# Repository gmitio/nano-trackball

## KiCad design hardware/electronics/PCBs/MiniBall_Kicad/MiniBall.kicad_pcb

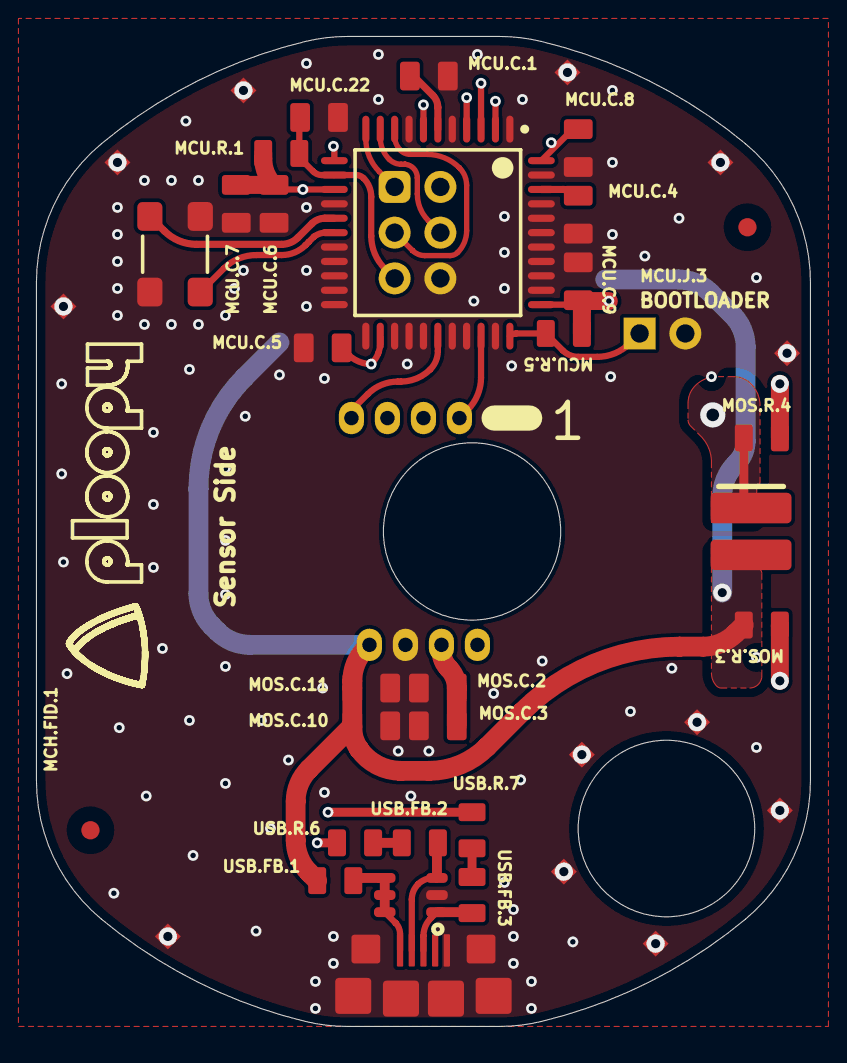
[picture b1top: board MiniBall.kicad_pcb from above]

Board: 4 copper layers, 43.0 x 55.0 mm, 44 parts (0 on the bottom side), 24 nets.

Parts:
MCH.FID.1, MCH.FID.2: IPC-7351 Fiducial 1mm; FIDUCIAL_1.5
MCH.LOGO.1: Ploopy logo, silkscreen; PloopyLogo
MCH.SP.1, MCH.SP.2, MCH.SP.3, MCH.SP.4, MCH.SP.5, MCH.SP.6, MCH.SP.7, MCH.SP.8, MCH.SP.9, MCH.SP.10, MCH.SP.11, MCH.SP.12: Spark Gap; SparkGap
MCU.C.1, MCU.C.4, MCU.C.5, MCU.C.6, MCU.C.7, MCU.C.8, MCU.C.9, MCU.C.22: 0805; 0805 - TALL
MCU.J.1: Atmel_ICSP; 6x2
MCU.J.3: HEADER2; 2x1
MCU.R.1, MCU.R.5: 0805
MCU.U.1: ATMEGA32U4RC-AU; ATmega32U4 - TQFP80P1200X1200X120-44N
MCU.Y.1: ECS-160-12-30B-AGM; LFXTAL055663BULK
MOS.C.2, MOS.C.3, MOS.C.10, MOS.C.11: 0805; 0805 - TALL
MOS.D.1: SIDELED-A67F
MOS.R.3, MOS.R.4: 0805
MOS.U.2: ADNS-5050
USB.FB.1, USB.FB.2, USB.FB.3: ACML-0805-601-T; 0805
USB.J.2: 10118192-0001LF
USB.R.6, USB.R.7: 0805
USB.Z.1: IP4220CZ6,125; PESD3V3S4UD - SOT95P275X110-6N

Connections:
GND: MCH.SP.1.1, MCH.SP.2.1, MCH.SP.3.1, MCH.SP.4.1, MCH.SP.5.1, MCH.SP.6.1, MCH.SP.7.1, MCH.SP.8.1, MCH.SP.9.1, MCH.SP.10.1, MCH.SP.11.1, MCH.SP.12.1, MCU.C.1.1, MCU.C.4.1, MCU.C.5.1, MCU.C.6.1, MCU.C.7.1, MCU.C.8.1, MCU.C.9.1, MCU.C.22.1, MCU.J.1.6, MCU.J.3.2, MCU.U.1.1, MCU.U.1.5, MCU.U.1.8, MCU.U.1.15, MCU.U.1.18, MCU.U.1.19, MCU.U.1.20, MCU.U.1.21, MCU.U.1.22, MCU.U.1.23, MCU.U.1.25, MCU.U.1.26, MCU.U.1.27, MCU.U.1.29, MCU.U.1.30, MCU.U.1.32, MCU.U.1.35, MCU.U.1.36, MCU.U.1.37, MCU.U.1.38, MCU.U.1.39, MCU.U.1.40, MCU.U.1.41, MCU.U.1.43, MCU.Y.1.2, MCU.Y.1.4, MOS.C.2.1, MOS.C.3.1, MOS.C.10.1, MOS.C.11.1, MOS.U.2.6, USB.J.2.5, USB.J.2.6, USB.Z.1.2
MISO: MCU.J.1.1, MCU.U.1.11
MOSI: MCU.J.1.4, MCU.U.1.10
NetMCU.C.1_2: MCU.C.1.2, MCU.U.1.6
NetMCU.C.4_2: MCU.C.4.2, MCU.U.1.42
NetMCU.J.3_1: MCU.J.3.1, MCU.R.5.1, MCU.U.1.33
NetMCU.U.1_3: MCU.U.1.3, USB.R.6.2
NetMCU.U.1_4: MCU.U.1.4, USB.R.7.2
NetMCU.U.1_12: MCU.U.1.12, MOS.U.2.8
NetMCU.U.1_16: MCU.U.1.16, MCU.Y.1.1
NetMCU.U.1_17: MCU.U.1.17, MCU.Y.1.3
NetMCU.U.1_28: MCU.U.1.28, MOS.U.2.4
NetMCU.U.1_31: MCU.U.1.31, MOS.U.2.1
NetMOS.C.2_2: MOS.C.2.2, MOS.C.3.2, MOS.U.2.7
NetMOS.D.1_C: MOS.D.1.C, MOS.R.4.1, MOS.U.2.2
NetMOS.R.3_1: MOS.R.3.1, MOS.R.4.2
NetUSB.FB.1_1: USB.FB.1.1, USB.J.2.1, USB.Z.1.4, USB.Z.1.5, USB.Z.1.6
NetUSB.FB.2_1: USB.FB.2.1, USB.J.2.2, USB.Z.1.3
NetUSB.FB.2_2: USB.FB.2.2, USB.R.6.1
NetUSB.FB.3_1: USB.FB.3.1, USB.J.2.3, USB.Z.1.1
NetUSB.FB.3_2: USB.FB.3.2, USB.R.7.1
SCLK: MCU.J.1.3, MCU.U.1.9
V_USB: MCU.C.5.2, MCU.C.6.2, MCU.C.7.2, MCU.C.8.2, MCU.C.9.2, MCU.J.1.2, MCU.R.1.2, MCU.R.5.2, MCU.U.1.2, MCU.U.1.7, MCU.U.1.14, MCU.U.1.24, MCU.U.1.34, MCU.U.1.44, MOS.C.10.2, MOS.C.11.2, MOS.D.1.A, MOS.R.3.2, MOS.U.2.5, USB.FB.1.2
~RESET: MCU.C.22.2, MCU.J.1.5, MCU.R.1.1, MCU.U.1.13, MOS.U.2.3

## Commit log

2025-09-20 Added Kicad-converted project files and Gerber files

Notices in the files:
hardware/electronics/PCBs/MiniBall_Kicad/MiniBall.kicad_pcb:
Licensed under CERN OHL v.1.2
